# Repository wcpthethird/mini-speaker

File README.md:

# Mini Speaker
## Overview
The goal of this project is to convert the guitar amplifer from LEGO set no. 21379 into a functional desktop speaker. Modifications include original and custom 3D-printed parts to support peripherals integration and PCB support. The LEGO amplifier is modeled in Fusion 360 in an effort to assist in the project's vizualization.

### [Design](3D_Model)
Features of the amp are exploited to increase the level of user-interaction with the device. Knobs along the front of the control panel house a small 3D-printed coupling device to actuate potentiometers that control volume and other effects. One of the knobs is replaced with a tactile switch to control the device's power state. A 2.5mm jack replaces its LEGO counterpart near the left end of the control panel, supported by two 3D-printed. An LED is placed behind the ruby near the right end of the control panel as a power indicator. A 57mm speaker is hidden within the speaker assembly, adhered to a 3D-printed plate at the center.

### [PCB](PCB)
The main PCB leverages an STM32F-series microcontroller and a 4-layer stackup with internal signal/power layers. It is pinned inside the rear enclosure of the amp using a spare knob from the control panel, supported by two 3D-printed bricks surrounding a USB-C port which powers the device. The auxilliary PCB with the ON/OFF switch is connected to the control panel PCB, which is connected to the main PCB via flex cable.

### [Firmware](MiniSpeaker_STM32)
Using ST's MCU software development tools, the main PCB is programmed to convert an analog signal to digital, apply some filtering and effects, and convert the digital signal back to analog where it is driven onto the output. Peripheral controls are also read via A/D converter and are implemented as volume and effects control parameters. Low-power mode, "standby," is leveraged to support the ON/OFF switch, events of which are read via GPIO and Wake-Up pins near-simultaneously (GPIO is hardware delayed).

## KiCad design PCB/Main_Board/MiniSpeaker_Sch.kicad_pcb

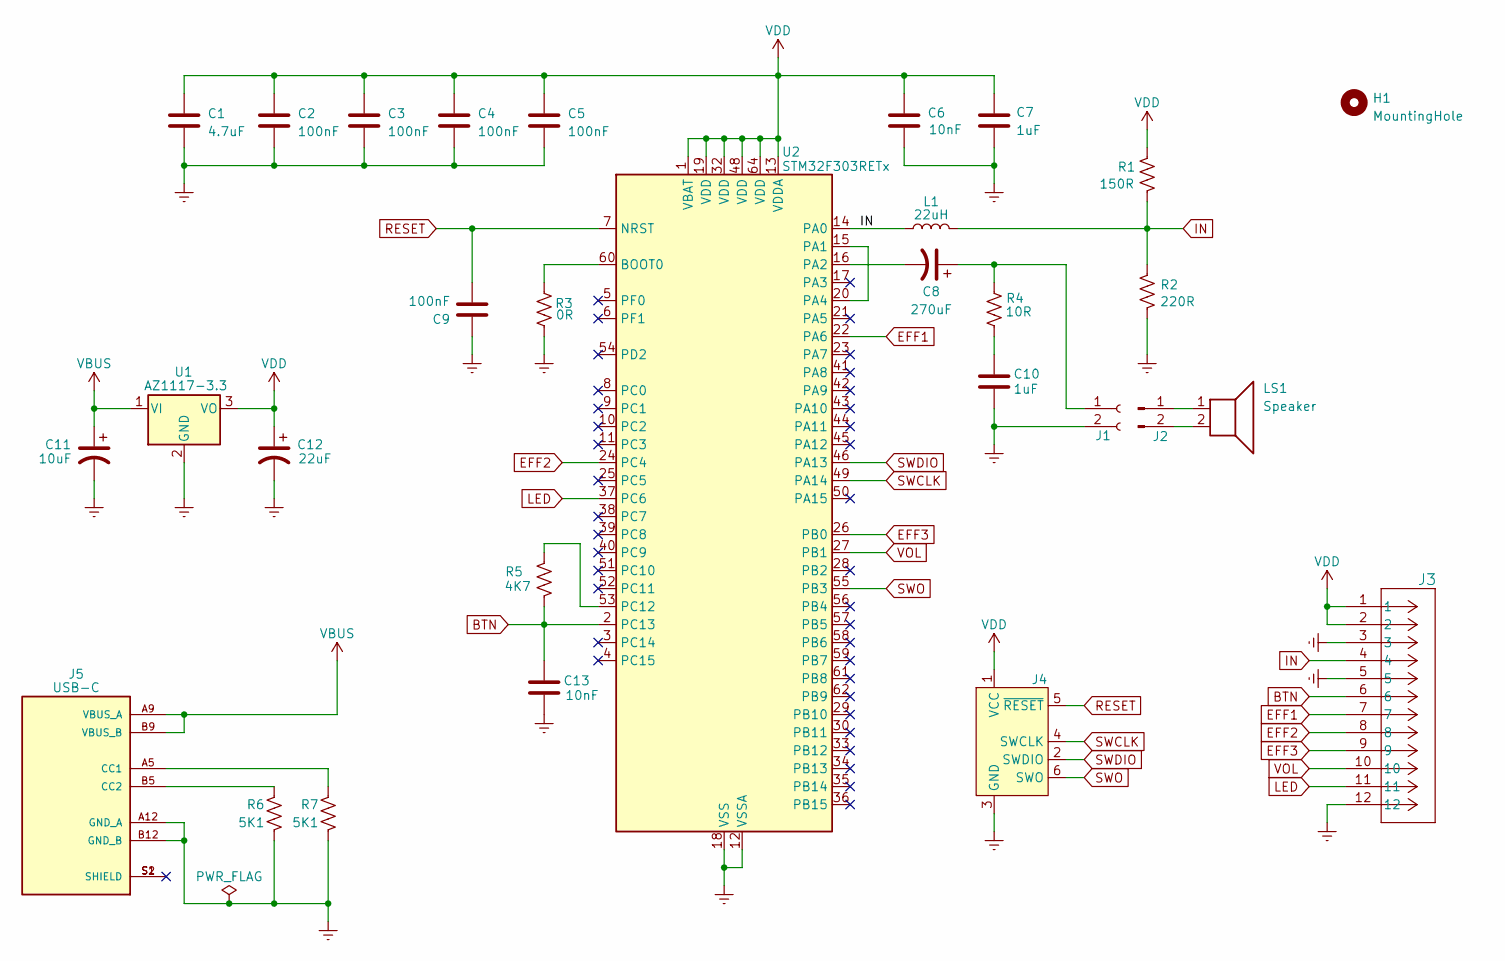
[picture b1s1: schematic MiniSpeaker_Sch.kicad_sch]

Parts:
C1: 4.7uF; C_0603_1608Metric; LCSC C152930
C2, C3, C4, C5, C9: 100nF; C_0402_1005Metric; LCSC C129131
C6, C13: 10nF; C_0402_1005Metric; LCSC C527020
C7, C10: 1uF; C_0402_1005Metric; LCSC C389008
C8: 270uF; CP_Elec_6.3x7.7; LCSC C178573
C11: 10uF; CP_EIA-3216-18_Kemet-A; LCSC C124856
C12: 22uF; CP_EIA-3216-18_Kemet-A; LCSC C124838
H1: MountingHole; MountingHole_4mm
J1: Conn_01x02_Socket; TE_440054-2_1x02_P2.00mm_Vertical
J2: Conn_01x02_Pin
J3: TE_Conn_1-1734248-2; TE_1-1734248-2; LCSC C590853
J4: SWD; PinHeader_2x03_P2.54mm_Vertical; LCSC C358692
J5: USB-C; GCT_USB4130-GF-A_REVA; LCSC C5187463
L1: 22uH; L_0603_1608Metric; LCSC C2041591
LS1: Speaker
R1: 150R; R_0402_1005Metric; LCSC C227304
R2: 220R; R_0402_1005Metric; LCSC C137899
R3: 0R; R_0402_1005Metric; LCSC C4288031
R4: 10R; R_0402_1005Metric; LCSC C144729
R5: 4K7; R_0402_1005Metric; LCSC C2935240
R6, R7: 5K1; R_0402_1005Metric; LCSC C144745
U1: AZ1117-3.3; SOT-223-3_TabPin2; LCSC C110474
U2: STM32F303RETx; LQFP-64_10x10mm_P0.5mm; LCSC C183214

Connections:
BTN: C13.2, J3.6, R5.1, U2.2 (PC13)
EFF1: J3.7, U2.22 (PA6)
EFF2: J3.8, U2.24 (PC4)
EFF3: J3.9, U2.26 (PB0)
Earth: C1.2, C2.2, C3.2, C4.2, C5.2, C6.2, C7.2, C9.1, C10.2, C11.2, C12.2, C13.1, J1.2, J3.3, J3.5, J3.12, J4.3 (GND), J5.A12 (GND_A), J5.B12 (GND_B), R2.2, R3.1, R6.2, R7.2, U1.2 (GND), U2.12 (VSSA), U2.18 (VSS), U2.31 (VSS), U2.47 (VSS), U2.63 (VSS)
IN: J3.4, L1.1, L1.2, R1.1, R2.1, U2.14 (PA0)
LED: J3.11, U2.37 (PC6)
unnamed: C10.1, R4.2
unnamed: C8.1, J1.1, R4.1
unnamed: J2.1, LS1.1
unnamed: J2.2, LS1.2
unnamed: J5.A5 (CC1), R7.1
unnamed: J5.B5 (CC2), R6.1
unnamed: R3.2, U2.60 (BOOT0)
unnamed: U2.15 (PA1), U2.20 (PA4)
unnamed: C8.2, U2.16 (PA2)
unnamed: R5.2, U2.53 (PC12)
RESET: C9.2, J4.5 (~RESET), U2.7 (NRST)
SWCLK: J4.4 (SWCLK), U2.49 (PA14)
SWDIO: J4.2 (SWDIO), U2.46 (PA13)
SWO: J4.6 (SWO), U2.55 (PB3)
VBUS: C11.1, J5.A9 (VBUS_A), J5.B9 (VBUS_B), U1.1 (VI)
VDD: C1.1, C2.1, C3.1, C4.1, C5.1, C6.1, C7.1, C12.1, J3.1, J3.2, J4.1 (VCC), R1.2, U1.3 (VO), U2.1 (VBAT), U2.13 (VDDA), U2.19 (VDD), U2.32 (VDD), U2.48 (VDD), U2.64 (VDD)
VOL: J3.10, U2.27 (PB1)

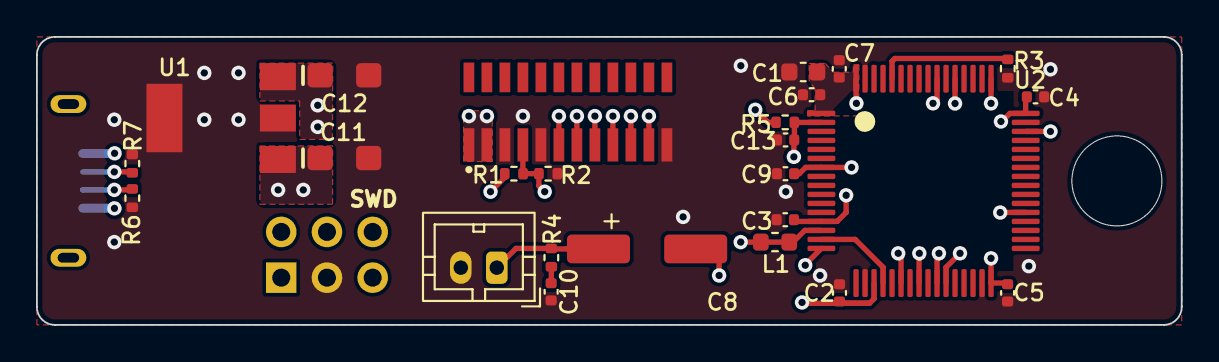
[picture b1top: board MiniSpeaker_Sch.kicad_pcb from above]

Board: 4 copper layers, 63.6 x 16.0 mm, 28 parts (1 on the bottom side), 22 nets.

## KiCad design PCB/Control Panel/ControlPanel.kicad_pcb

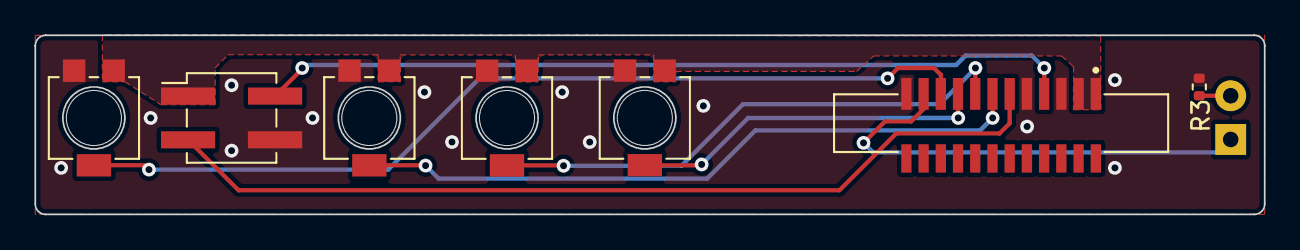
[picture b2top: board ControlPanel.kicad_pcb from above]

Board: 2 copper layers, 71.4 x 10.4 mm, 8 parts (0 on the bottom side), 10 nets.

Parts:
D1: LED; LED_D3.0mm_Horizontal_O6.35mm_Z2.0mm
J1: Conn_01x04_Pin; PinHeader_2x02_P2.54mm_Vertical_SMD
J2: TE_Conn_1-1734248-2; TE_1-1734248-2
R3: 3K3; R_0402_1005Metric
RV1, RV2, RV3, RV4: R_Potentiometer_US; Potentiometer_Bourns_3314R-1_Vertical_Hole

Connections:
BTN: J1.3, J2.6
EFF1: J2.7, RV2.2
EFF2: J2.8, RV3.2
EFF3: J2.9, RV4.2
Earth: J1.4, J2.3, J2.5, J2.12, R3.2, RV1.3, RV2.3, RV3.3, RV4.3
IN: J1.2, J2.4
LED: D1.1 (K), J2.11
unnamed: D1.2 (A), R3.1
VDD: J1.1, J2.1, J2.2, RV1.1, RV2.1, RV3.1, RV4.1
VOL: J2.10, RV1.2

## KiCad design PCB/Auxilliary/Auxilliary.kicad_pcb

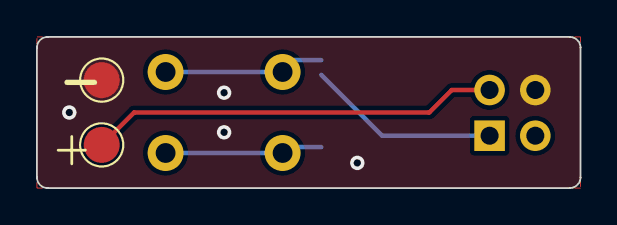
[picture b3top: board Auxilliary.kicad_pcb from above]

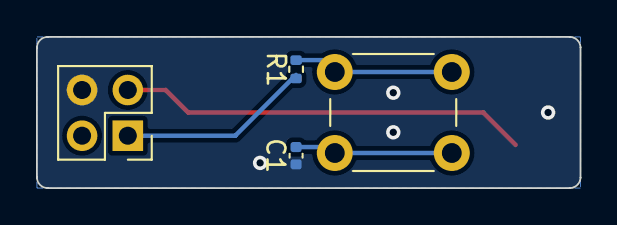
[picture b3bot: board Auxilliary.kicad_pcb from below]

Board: 2 copper layers, 30.2 x 8.4 mm, 6 parts (4 on the bottom side), 5 nets.

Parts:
C1: 1uF; C_0402_1005Metric
J1, J2: Conn_01x01_Socket; TestPoint_Pad_D2.0mm
J3: Conn_01x04_Socket; PinSocket_2x02_P2.54mm_Vertical
R1: 4K7; R_0402_1005Metric
SW1: SW_Push; SW_PUSH_6mm_H13mm

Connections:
Earth: C1.2, J2.1, J3.4
IN: J1.1, J3.2
unnamed: C1.1, SW1.1
unnamed: R1.1, SW1.2
VDD: J3.1, R1.2

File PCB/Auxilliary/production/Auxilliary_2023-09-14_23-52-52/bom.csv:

Designator,Footprint,Quantity,Value,LCSC Part #
C1,0402,1,1uF,C389008
"J1, J2",TestPoint_Pad_D2.0mm,2,Conn_01x01_Socket,
J3,PinSocket_2x02_P2.54mm_Vertical,1,Conn_01x04_Socket,
R1,0402,1,4K7,C2935240
SW1,SW_PUSH_6mm_H13mm,1,SW_Push,

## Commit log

2023-09-16 Add Main Board files
2023-09-16 Add Control Panel files
2023-09-16 Add Auxilliary files
2023-09-16 Add STM32 code files
2023-09-16 Add Reference files
2023-09-16 Add Simulink files
2023-09-16 Add validation files
2023-09-16 Update Reference files
2023-09-16 Delete Reference/ADCConfig.png
    Obsolete
2023-09-16 Add 3D Model files
2023-09-16 Add exploded Control Panel model
2023-09-16 Chore: Clarify standby comment
2023-09-16 Chore: Clarify standby comment (#1)
2023-09-16 Chore: Consolidate PCB files
2023-09-16 Chore: Consolidate PCB files (#2)
    * Chore: Clarify standby comment
    * Chore: Consolidate PCB files
2023-09-17 Add "Print" folder to 3D model directory
    Clean up inconsistent file names
